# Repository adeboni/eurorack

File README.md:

This repository stores various eurorack module designs I've made.

* BT Module: Allows you to pair your phone or computer and outputs stereo audio
* Dodecamodulator: 12 individually configurable LFOs through an onboard UI or through Bluetooth
* Geiger Clock Module: Uses a Geiger–Müller tube to generate pulses
* Google Assistant Module: A Google Home Mini in a eurorack form-factor
* Neopixel Controller Module: Can control neopixel rainbow cycle speed, brightness, and VU-meter-style amplitude with CV
* CS:GO Game State Integration Server: Receives events from CS:GO and enables gate outputs based on game states
* Safety Valve: Update of the GSMN Safety Safety Valve module with a trimmer to remove op-amp offset and added a socket for the tube
* ECG: Outputs a waveform from ECG electrodes plus a gate output with threshold adjustment

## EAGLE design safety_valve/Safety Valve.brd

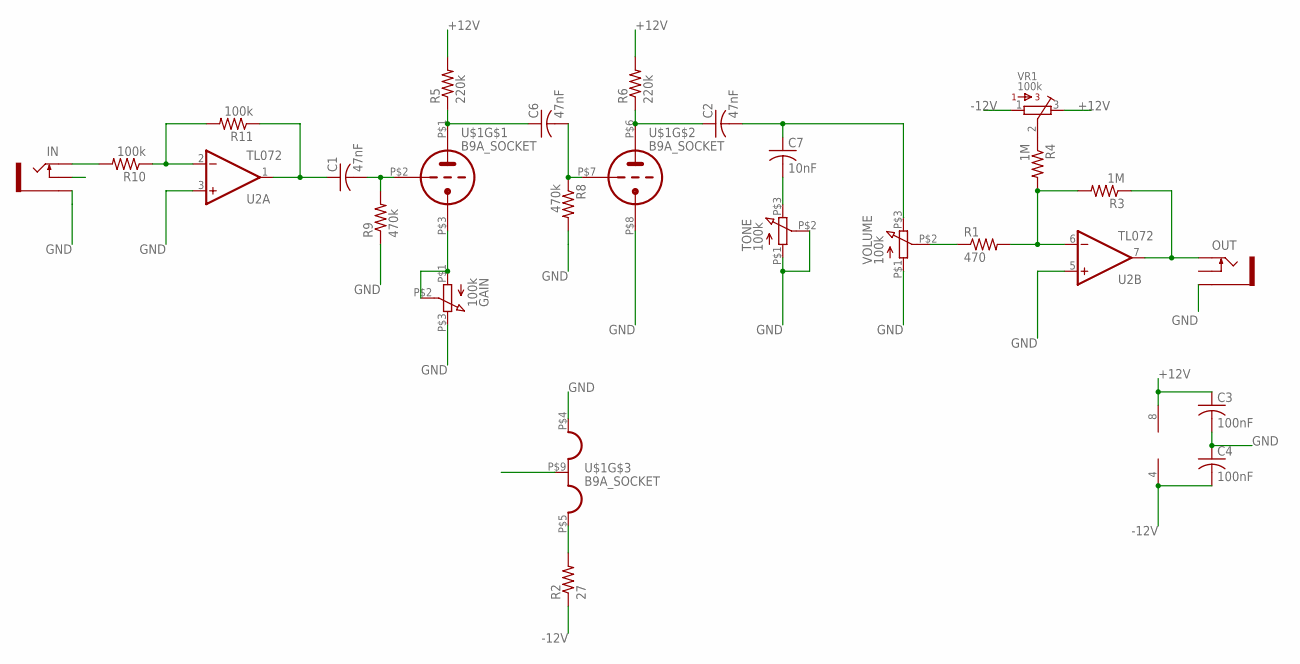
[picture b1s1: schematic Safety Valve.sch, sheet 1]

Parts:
C1, C2, C6: 47nF; C025-024X044
C3, C4: 100nF; C025-024X044
C7: 10nF; C050-024X044
GAIN: 100k; POTENTIOMETER_9MM
IN: SOCKET_MONO_3.5MMPJ301M-12; PJ301M-12
OUT: SOCKET_MONO_3.5MMPJ301M-12; PJ301M-12
R1: 470; 0207/10
R2: 27; 0207/15
R3, R4: 1M; 0207/10
R5, R6: 220k; 0207/10
R8, R9: 470k; 0207/10
R10, R11: 100k; 0207/10
TONE: 100k; POTENTIOMETER_9MM
U2: TL072; DIL08-SML
U$1: B9A_SOCKET
VOLUME: 100k; POTENTIOMETER_9MM
VR1: 100k; BOURNS_3362P_TRIMMER

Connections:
+12V: C3.1, R5.2, R6.2, U2.8 (V+), VR1.3; also elsewhere on the board
-12V: C4.2, R2.1, U2.4 (V-), VR1.1; also elsewhere on the board
GND: C3.2, C4.1, GAIN.P$3 (3), IN.GND (SLEEVE), OUT.GND (SLEEVE), R8.2, R9.1, TONE.P$1 (1), TONE.P$2 (2), U2.3 (+IN), U2.5 (+IN), U$1.P$4 (H1), U$1.P$8 (TK), VOLUME.P$1 (1); also elsewhere on the board
unnamed: GAIN.P$1 (1), GAIN.P$2 (2), U$1.P$3 (TK)
unnamed: R1.2, R3.2, R4.2, U2.6 (-IN)
unnamed: C2.2, C7.1, VOLUME.P$3 (3)
unnamed: OUT.TIP, R3.1, U2.7 (OUT)
unnamed: C2.1, R6.1, U$1.P$6 (TA)
unnamed: C6.1, R5.1, U$1.P$1 (TA)
unnamed: C1.2, R9.2, U$1.P$2 (TG)
unnamed: R4.1, VR1.2
unnamed: C1.1, R11.1, U2.1 (OUT)
unnamed: R2.2, U$1.P$5 (H3)
unnamed: C6.2, R8.1, U$1.P$7 (TG)
unnamed: IN.TIP, R10.2
unnamed: C7.2, TONE.P$3 (3)
unnamed: R10.1, R11.2, U2.2 (-IN)
unnamed: R1.1, VOLUME.P$2 (2)

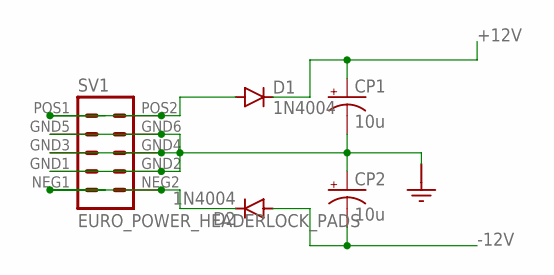
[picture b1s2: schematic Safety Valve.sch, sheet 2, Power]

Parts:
CP1, CP2: 10u; SANYO-OSCON_D
D1, D2: 1N4004; DO41-10
SV1: EURO_POWER_HEADERLOCK_PADS; EURO_PWR_HEADER_LOCK

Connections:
+12V: CP1.+, D1.C; also elsewhere on the board
-12V: CP2.-, D2.A; also elsewhere on the board
GND: CP1.-, CP2.+, SV1.GND1 (4), SV1.GND2 (3), SV1.GND3 (6), SV1.GND4 (5), SV1.GND5 (8), SV1.GND6 (7); also elsewhere on the board
unnamed: D1.A, SV1.POS1 (10), SV1.POS2 (9)
unnamed: D2.C, SV1.NEG1 (2), SV1.NEG2 (1)

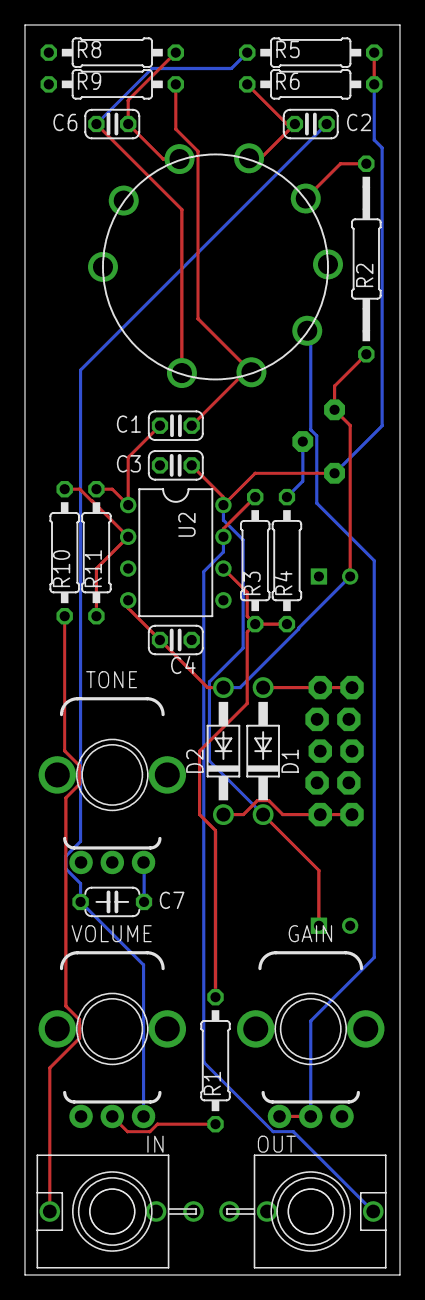
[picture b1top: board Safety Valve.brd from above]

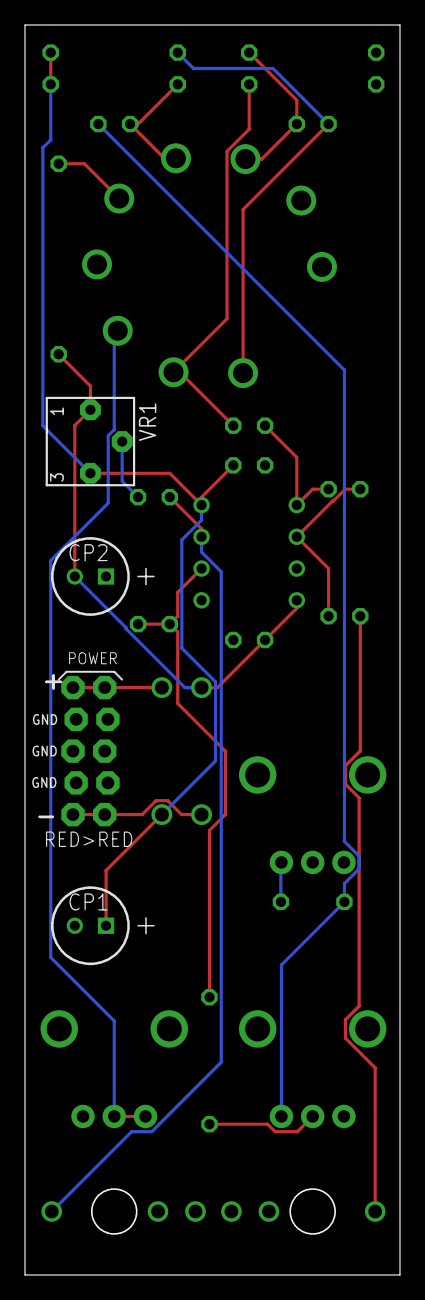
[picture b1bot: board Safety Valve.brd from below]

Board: 2 copper layers, 29.9 x 99.9 mm, 29 parts (4 on the bottom side), 20 nets.

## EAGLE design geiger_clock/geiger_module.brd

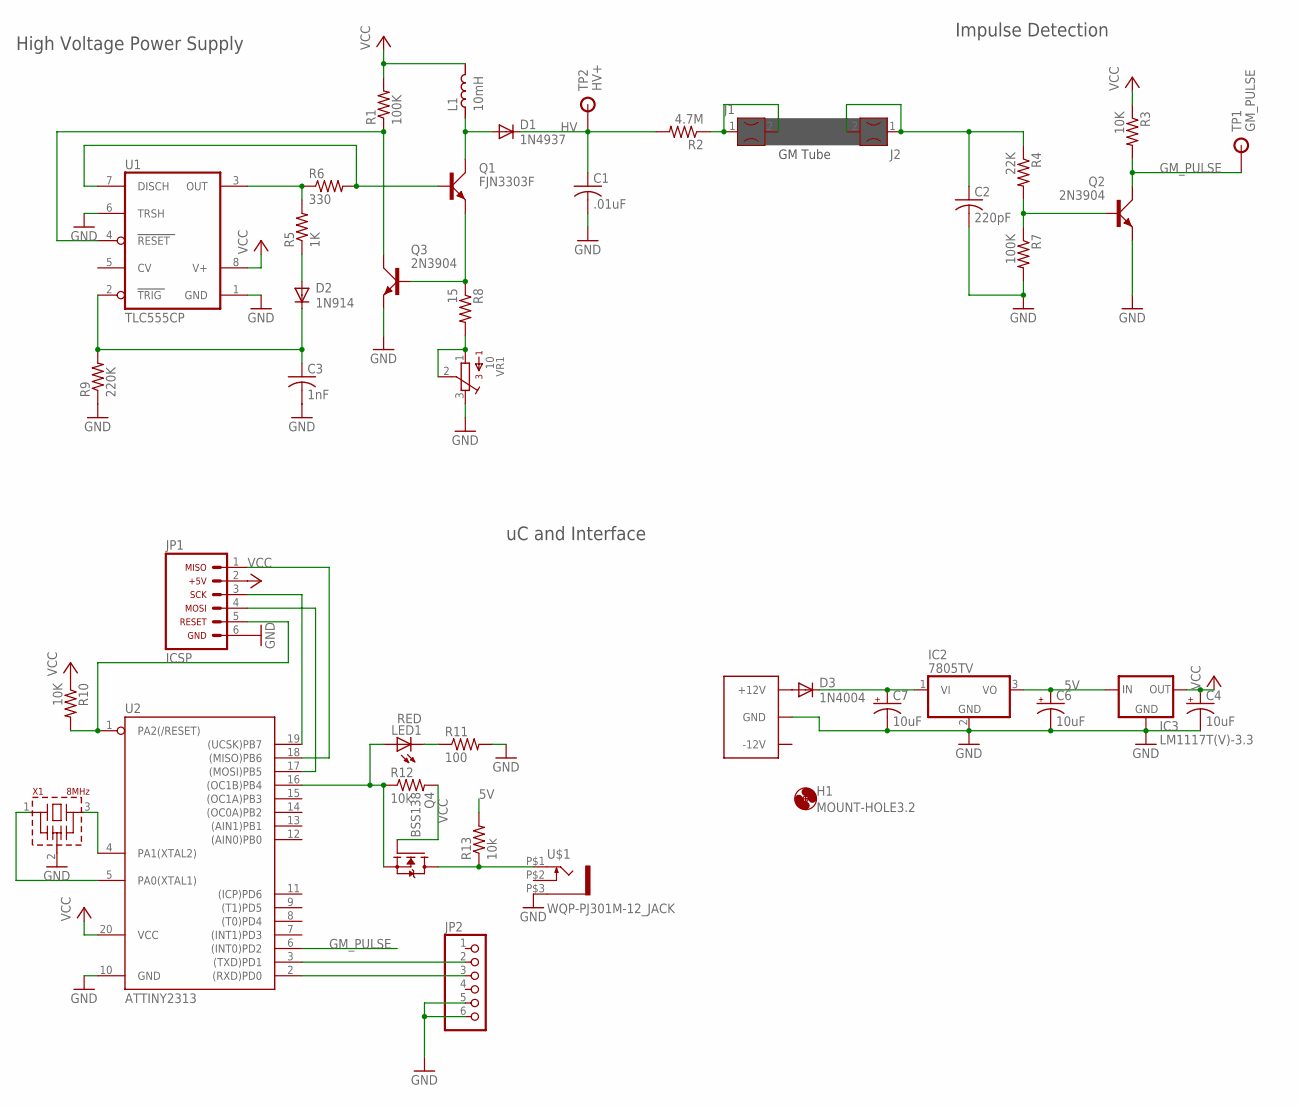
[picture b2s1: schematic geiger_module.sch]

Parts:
C1: .01uF; C102-043X133
C2: 220pF; C050-030X075
C3: 1nF; C050-025X075
C4, C6, C7: 10uF; CPOL-RADIAL-2.5MM-5MM
C8: EURO_POWER_LOCKSKINNY; EURO_POWER_HEADER
D1: 1N4937; DO41-10
D2: 1N914; DO35-7
D3: 1N4004; DO41-10
H1: MOUNT-HOLE3.2; 3,2
IC2: 7805TV; TO220V
IC3: LM1117T(V)-3.3; TO220V
J1, J2: FUSECLIPPCMOUNT; FUSECLIP_PCMOUNT
JP1: ARDUINO_CONN-ICSP; CONN-2X03
JP2: PINHD-1X6; 1X06
L1: 10mH; ELC09D
LED1: RED; LED5MM
Q1: FJN3303F; TO92C
Q2, Q3: 2N3904; TO92D
Q4: BSS138; SOT23
R1, R7: 100K; 0207/10
R2: 4.7M; 0207/10
R3, R10: 10K; 0207/10
R4: 22K; 0207/10
R5: 1K; 0207/10
R6: 330; 0207/10
R8: 15; 0207/10
R9: 220K; 0207/10
R11: 100; 0207/10
R12, R13: 10k; 0207/10
TP1: GM_PULSE; TP_PTH
TP2: HV+; TP_PTH
U1: TLC555CP; DIL08
U2: ATTINY2313; DIL20
U$1: WQP-PJ301M-12_JACK
VR1: 10; 3386P
X1: 8MHz; CSTLA_T

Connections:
5V: C6.1 (+), IC2.3 (VO), IC3.3 (IN), R13.2
12V: C7.1 (+), D3.C, IC2.1 (VI)
GM_PULSE: Q2.C, R3.2, TP1.P$1, U2.6 ((INT0)PD2)
GND: C1.2, C2.2, C3.2, C4.2 (-), C6.2 (-), C7.2 (-), C8.3 (GND), C8.4 (GND), C8.5 (GND), C8.6 (GND), C8.7 (GND), C8.8 (GND), IC2.2 (GND), IC3.1 (GND), JP1.6, JP2.5, JP2.6, Q2.E, Q3.E, R7.2, R9.1, R11.2, U1.1 (GND), U1.6 (TRSH), U2.10 (GND), U$1.P$3 (1), VR1.3, X1.2 (VSS)
HV: C1.1, D1.C, R2.2, TP2.P$1
unnamed: D2.A, R5.1
unnamed: JP1.5, R10.2, U2.1 (PA2(/RESET))
unnamed: Q3.C, R1.1, U1.4 (RESET)
unnamed: C8.9 (+12V), C8.10 (+12V), D3.A
unnamed: JP1.3, U2.19 ((UCSK)PB7)
unnamed: JP2.2, U2.3 ((TXD)PD1)
unnamed: JP2.3, U2.2 ((RXD)PD0)
unnamed: Q1.B, R6.2, U1.7 (DISCH)
unnamed: C3.1, D2.C, R9.2, U1.2 (TRIG)
unnamed: R5.2, R6.1, U1.3 (OUT)
unnamed: Q1.E, Q3.B, R8.1
unnamed: D1.A, L1.1, Q1.C
unnamed: JP1.1, U2.18 ((MISO)PB6)
unnamed: Q2.B, R4.2, R7.1
unnamed: J1.1, J1.2, R2.1
unnamed: JP1.4, U2.17 ((MOSI)PB5)
unnamed: U2.4 (PA1(XTAL2)), X1.3
unnamed: U2.5 (PA0(XTAL1)), X1.1
unnamed: LED1.K (C), R11.1
unnamed: R8.2, VR1.1, VR1.2
unnamed: C2.1, J2.1, J2.2, R4.1
PIN16: LED1.A, Q4.2 (S), R12.1, U2.16 ((OC1B)PB4)
PIN165V: Q4.3 (D), R13.1, U$1.P$1 (2)
VCC: C4.1 (+), IC3.2 (OUT), JP1.2, L1.2, Q4.1 (G), R1.2, R3.1, R10.1, R12.2, U1.8 (V+), U2.20 (VCC)

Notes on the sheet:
GM Tube
High Voltage Power Supply
Impulse Detection
uC and Interface

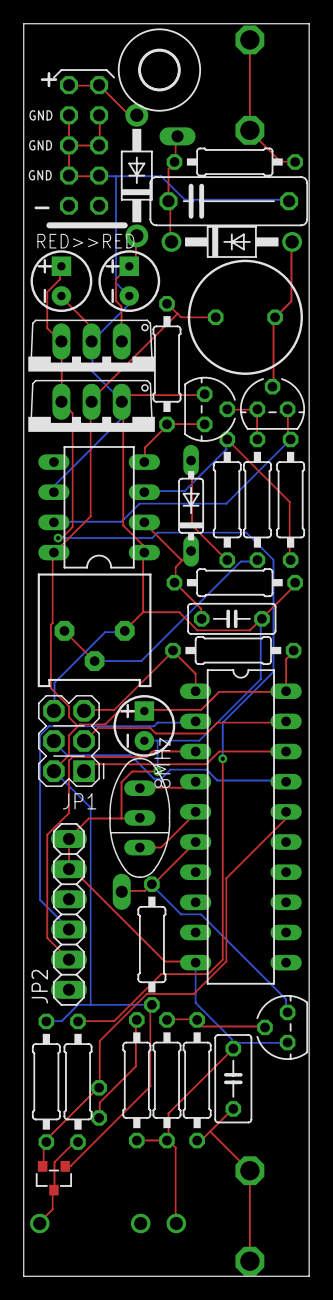
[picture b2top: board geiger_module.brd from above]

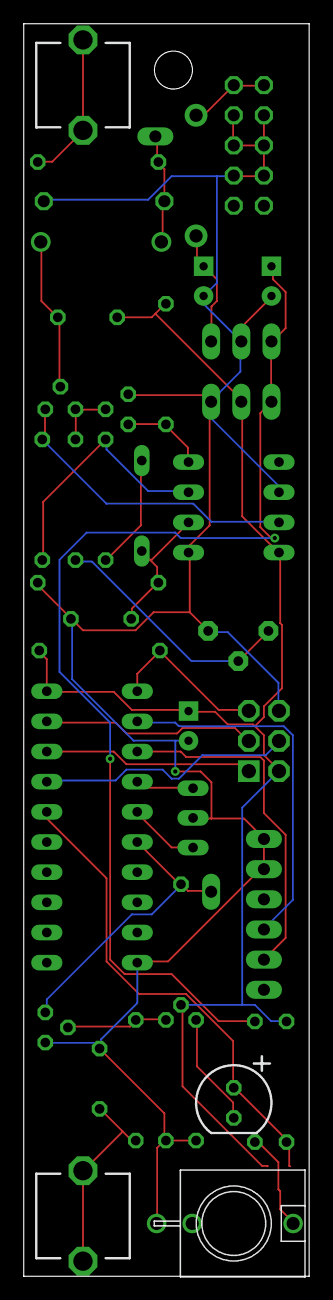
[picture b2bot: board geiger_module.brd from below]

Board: 2 copper layers, 24.0 x 105.5 mm, 43 parts (4 on the bottom side), 29 nets.

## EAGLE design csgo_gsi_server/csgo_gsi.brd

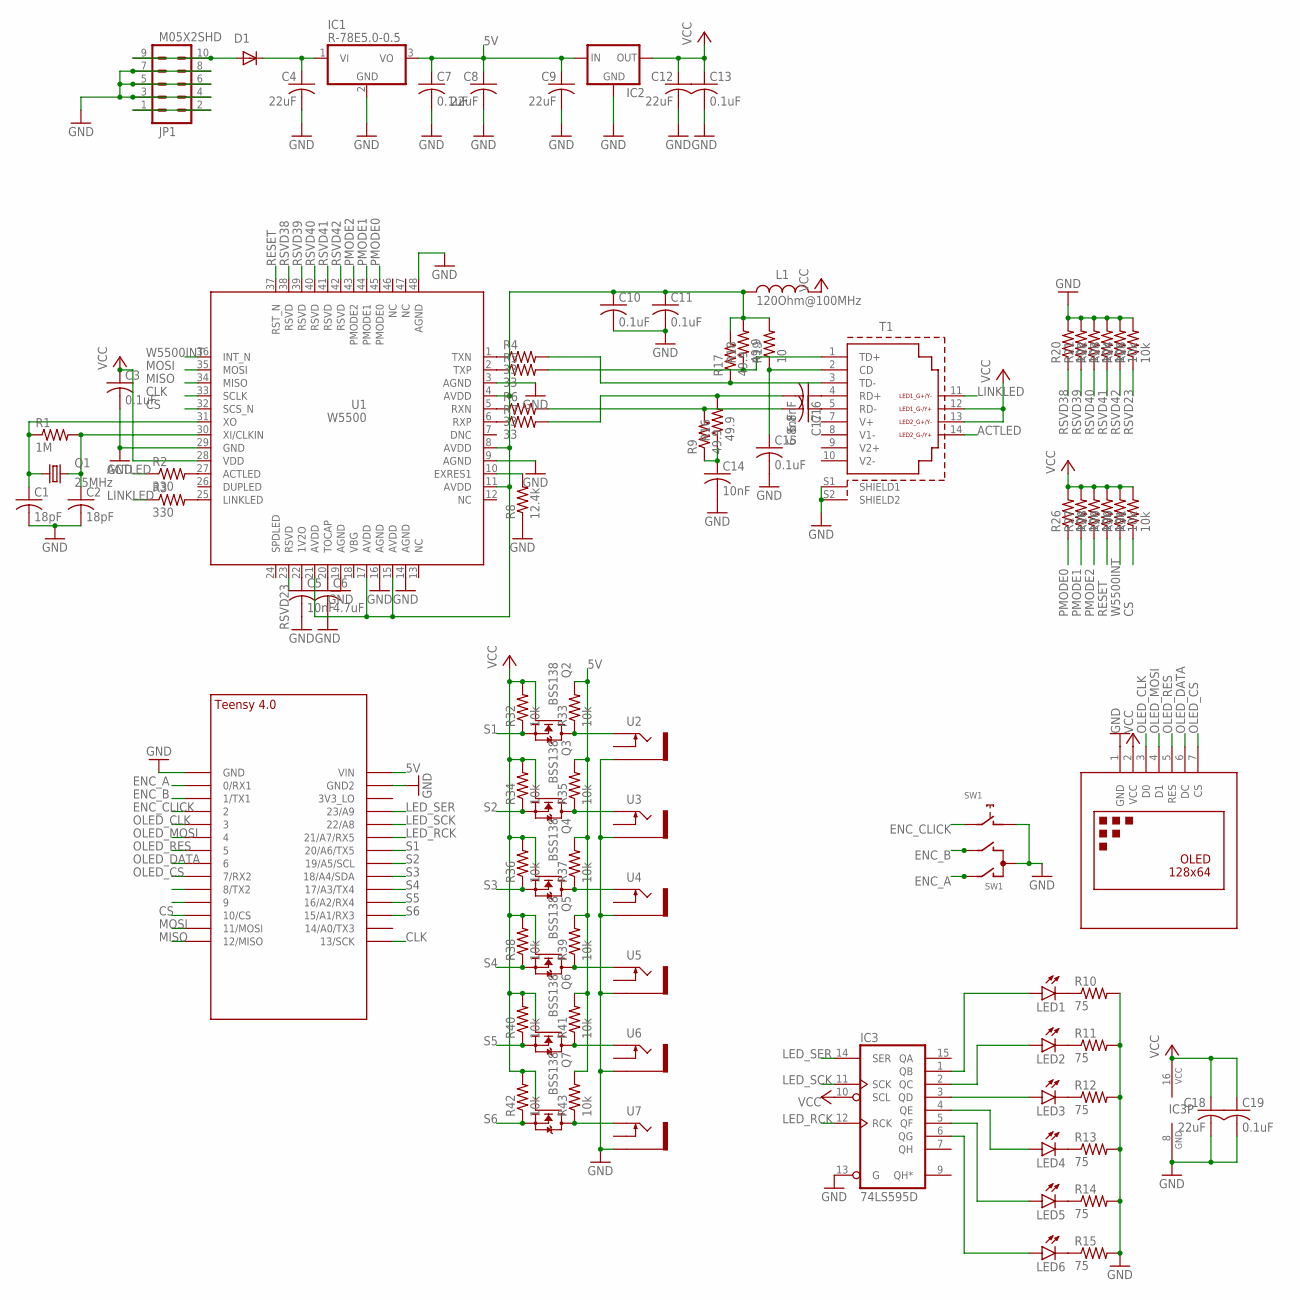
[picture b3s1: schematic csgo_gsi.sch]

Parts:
C1, C2: 18pF; C0603
C3, C7, C10, C11, C13, C15, C19: 0.1uF; C0603
C4, C8, C9, C12, C18: 22uF; C1206
C5, C14: 10nF; C0603
C6: 4.7uF; C0603
C16, C17: 6.8nF; C0603
D1: 1N5819HW; SOD123
IC1: R-78E5.0-0.5; WE78
IC2: LM1117; SOT223
IC3: 74LS595D; SO16
JP1: M05X2SHD; 2X5-SHROUDED
L1: 120Ohm@100MHz; WE-CBF_0603(W=2.2)
LED1, LED2, LED3, LED4, LED5, LED6: LED3MM
OLED1: DISPLAY-OLED-128X64
Q1: 25MHz; 3.2X2.5_KX-7
Q2, Q3, Q4, Q5, Q6, Q7: BSS138; SOT23
R1: 1M; R0603
R2, R3: 330; R0603
R4, R5, R6, R7: 33; R0603
R8: 12.4k; R0603
R9, R16, R17, R18: 49.9; R0603
R10, R11, R12, R13, R14, R15: 75; R0603
R19: 10; R0603
R20, R21, R22, R23, R24, R25, R26, R27, R28, R29, R30, R31, R32, R33, R34, R35, R36, R37, R38, R39, R40, R41, R42, R43: 10k; R0603
SW1: Encoder; ALPS_EC12E_SW
T1: WE-RJ45_74984104401; 74984104401
U1: W5500
U2, U3, U4, U5, U6, U7: THONKICONNNEW; WQP-PJ301M-12_JACK
U$1: TEENSY_4.0-BASIC

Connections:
5V: C7.1, C8.1, C9.1, IC1.3 (VO), IC2.3 (IN), R33.2, R35.2, R37.2, R39.2, R41.2, R43.2, U$1.VIN
12V: C4.1, D1.C, IC1.1 (VI)
ACTLED: R2.1, T1.14 (LED2_Y+/G-)
CLK: U1.33 (SCLK), U$1.13/SCK
CS: R31.1, U1.32 (SCS_N), U$1.10/CS
ENC_A: SW1.A, U$1.0/RX (0/RX1)
ENC_B: SW1.B, U$1.1/TX (1/TX1)
ENC_CLICK: SW1.E (2), U$1.2
GND: C1.2, C2.2, C3.2, C4.2, C5.2, C6.2, C7.2, C8.2, C9.2, C10.2, C11.2, C12.2, C13.2, C14.2, C15.2, C18.2, C19.2, IC1.2 (GND), IC2.1 (GND), IC3.8 (GND), IC3.13 (G), JP1.3, JP1.4, JP1.5, JP1.6, JP1.7, JP1.8, OLED1.1 (GND), R8.1, R10.2, R11.2, R12.2, R13.2, R14.2, R15.2, R20.2, R21.2, R22.2, R23.2, R24.2, R25.2, SW1.C, SW1.D (1), T1.S1 (SHIELD1), T1.S2 (SHIELD2), U1.3 (AGND), U1.9 (AGND), U1.14 (AGND), U1.16 (AGND), U1.19 (AGND), U1.29 (GND), U1.48 (AGND), U2.P$3_SLEEVE (SLEEVE), U3.P$3_SLEEVE (SLEEVE), U4.P$3_SLEEVE (SLEEVE), U5.P$3_SLEEVE (SLEEVE), U6.P$3_SLEEVE (SLEEVE), U7.P$3_SLEEVE (SLEEVE), U$1.GND
LED1: IC3.1 (QB), LED1.A
LED2: IC3.2 (QC), LED2.A
LED3: IC3.3 (QD), LED3.A
LED4: IC3.4 (QE), LED4.A
LED5: IC3.5 (QF), LED5.A
LED6: IC3.6 (QG), LED6.A
LED_RCK: IC3.12 (RCK), U$1.21/A7 (21/A7/RX5)
LED_SCK: IC3.11 (SCK), U$1.22/A8
LED_SER: IC3.14 (SER), U$1.23/A9
LINKLED: R3.1, T1.11 (LED1_Y-/G+)
MISO: U1.34 (MISO), U$1.12/MISO
MOSI: U1.35 (MOSI), U$1.11/MOSI
unnamed: C5.1, U1.22 (1V2O)
unnamed: C6.1, U1.20 (TOCAP)
unnamed: R5.2, R18.1, T1.1 (TD+)
unnamed: R4.2, R17.1, T1.3 (TD-)
unnamed: R3.2, U1.25 (LINKLED)
unnamed: R2.2, U1.27 (ACTLED)
unnamed: R8.2, U1.10 (EXRES1)
unnamed: R4.1, U1.1 (TXN)
unnamed: R5.1, U1.2 (TXP)
unnamed: R6.1, U1.5 (RXN)
unnamed: R7.1, U1.6 (RXP)
unnamed: C16.1, T1.4 (RD+)
unnamed: C17.1, T1.5 (RD-)
unnamed: C16.2, R7.2, R16.2
unnamed: C17.2, R6.2, R9.2
unnamed: C14.1, R9.1, R16.1
unnamed: C1.1, Q1.1, R1.1, U1.31 (XO)
unnamed: C15.1, R19.1, T1.2 (CD)
unnamed: C10.1, C11.1, L1.1, R17.2, R18.2, R19.2, U1.4 (AVDD), U1.8 (AVDD), U1.11 (AVDD), U1.15 (AVDD), U1.17 (AVDD), U1.21 (AVDD)
unnamed: C2.1, Q1.3 (2), R1.2, U1.30 (XI/CLKIN)
unnamed: LED1.K (C), R10.1
unnamed: Q2.3 (D), R33.1, U2.P$1_TIP (TIP)
unnamed: LED2.K (C), R11.1
unnamed: Q3.3 (D), R35.1, U3.P$1_TIP (TIP)
unnamed: LED3.K (C), R12.1
unnamed: Q4.3 (D), R37.1, U4.P$1_TIP (TIP)
unnamed: LED4.K (C), R13.1
unnamed: Q5.3 (D), R39.1, U5.P$1_TIP (TIP)
unnamed: LED5.K (C), R14.1
unnamed: Q6.3 (D), R41.1, U6.P$1_TIP (TIP)
unnamed: LED6.K (C), R15.1
unnamed: Q7.3 (D), R43.1, U7.P$1_TIP (TIP)
unnamed: D1.A, JP1.9, JP1.10
unnamed: JP1.1, JP1.2
OLED_CLK: OLED1.3 (D0), U$1.3/CANTX (3)
OLED_CS: OLED1.7 (CS), U$1.7 (7/RX2)
OLED_DATA: OLED1.6 (DC), U$1.6
OLED_MOSI: OLED1.4 (D1), U$1.4/CANRX (4)
OLED_RES: OLED1.5 (RES), U$1.5
PMODE0: R26.1, U1.45 (PMODE0)
PMODE1: R27.1, U1.44 (PMODE1)
PMODE2: R28.1, U1.43 (PMODE2)
RESET: R29.1, U1.37 (RST_N)
RSVD23: R25.1, U1.23 (RSVD)
RSVD38: R20.1, U1.38 (RSVD)
RSVD39: R21.1, U1.39 (RSVD)
RSVD40: R22.1, U1.40 (RSVD)
RSVD41: R23.1, U1.41 (RSVD)
RSVD42: R24.1, U1.42 (RSVD)
S1: Q2.2 (S), R32.1, U$1.20/A6 (20/A6/TX5)
S2: Q3.2 (S), R34.1, U$1.19/A5/SCL
S3: Q4.2 (S), R36.1, U$1.18/A4/SDA
S4: Q5.2 (S), R38.1, U$1.17/A3 (17/A3/TX4)
S5: Q6.2 (S), R40.1, U$1.16/A2 (16/A2/RX4)
S6: Q7.2 (S), R42.1, U$1.15/A1 (15/A1/RX3)
VCC: C3.1, C12.1, C13.1, C18.1, C19.1, IC2.2 (OUT), IC3.10 (SCL), IC3.16 (VCC), L1.2, OLED1.2 (VCC), Q2.1 (G), Q3.1 (G), Q4.1 (G), Q5.1 (G), Q6.1 (G), Q7.1 (G), R26.2, R27.2, R28.2, R29.2, R30.2, R31.2, R32.2, R34.2, R36.2, R38.2, R40.2, R42.2, T1.12 (LED1_Y+/G-), T1.13 (LED2_Y-/G+), U1.28 (VDD)
W5500INT: R30.1, U1.36 (INT_N)

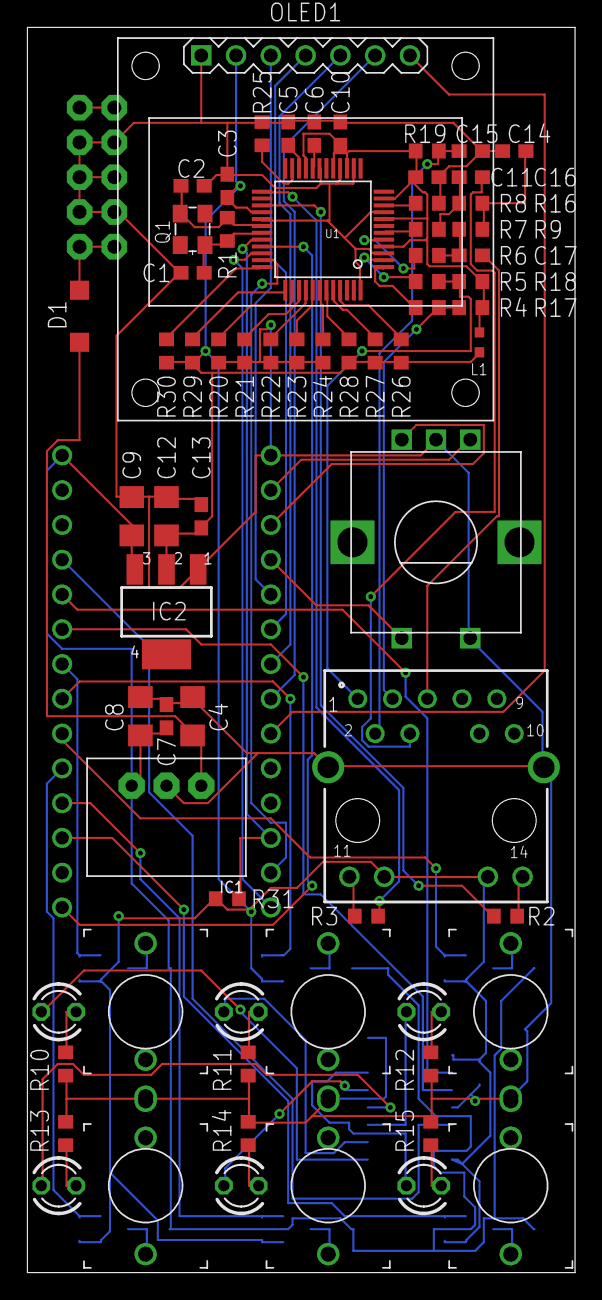
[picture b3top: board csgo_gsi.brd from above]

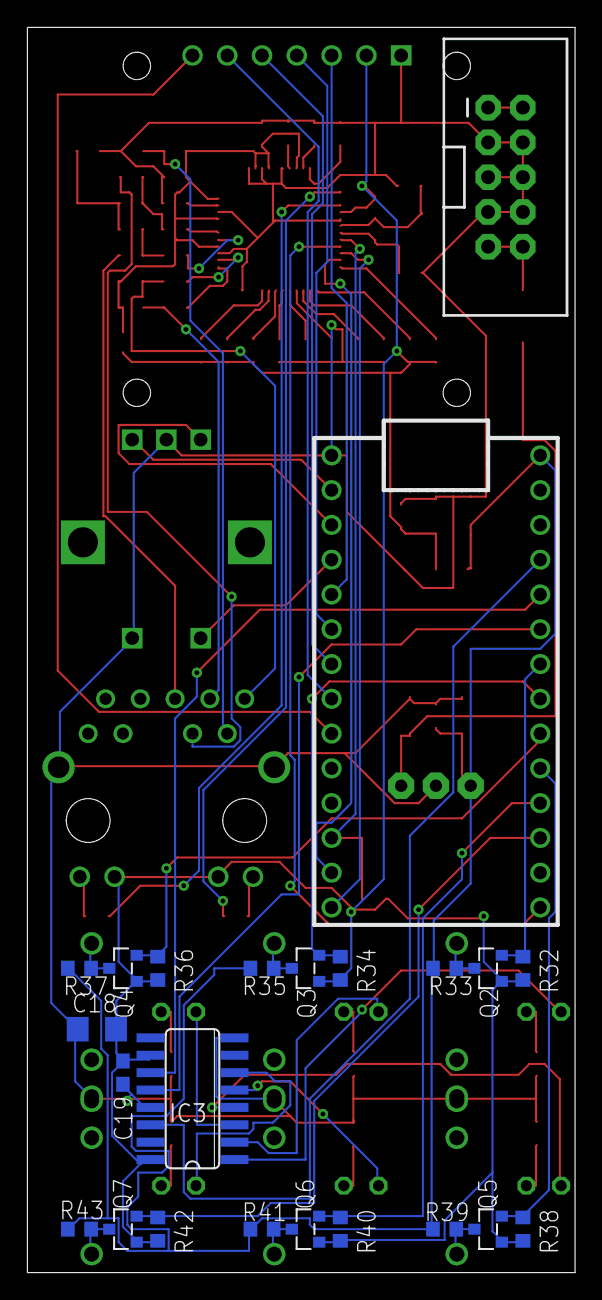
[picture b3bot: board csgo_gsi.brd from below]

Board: 2 copper layers, 40.0 x 91.0 mm, 92 parts (23 on the bottom side), 78 nets.

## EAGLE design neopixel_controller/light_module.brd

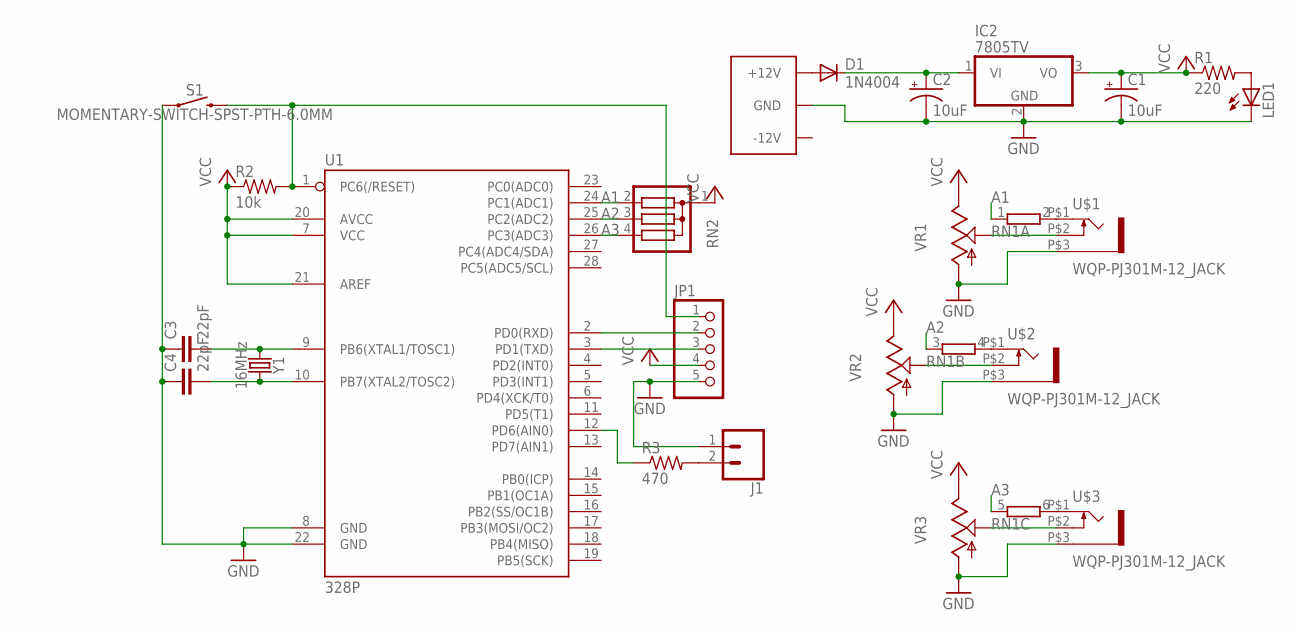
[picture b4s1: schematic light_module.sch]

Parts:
C1, C2: 10uF; CPOL-RADIAL-2.5MM-5MM
C3, C4: 22pF; CAP-PTH-2.54
C5: EURO_POWER_LOCKSKINNY; EURO_POWER_HEADER
D1: 1N4004; DO41-10
IC2: 7805TV; TO220V
J1: CONN_02SPRING-2.54-RA; SPRINGTERMINAL-2.54MM-2
JP1: PINHD-1X5; 1X05
LED1: LED5MM
R1: 220; 0207/2V
R2: 10k; 0207/2V
R3: 470; 0207/2V
RN1: E3R; SIL6
RN2: G03R; SIL4
S1: MOMENTARY-SWITCH-SPST-PTH-6.0MM; TACTILE_SWITCH_PTH_6.0MM
U1: 328P; DIP28
U$1, U$2, U$3: WQP-PJ301M-12_JACK
VR1, VR2, VR3: 9MM_SNAP-IN_POT_; 9MM_SNAP-IN_POT
Y1: 16MHz; HC49US

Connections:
A1: RN1.1, RN2.2, U1.24 (PC1(ADC1))
A2: RN1.3 (1), RN2.3, U1.25 (PC2(ADC2))
A3: RN1.5 (1), RN2.4, U1.26 (PC3(ADC3))
GND: C1.2 (-), C2.2 (-), C3.1, C4.1, C5.3 (GND), C5.4 (GND), C5.5 (GND), C5.6 (GND), C5.7 (GND), C5.8 (GND), IC2.2 (GND), J1.1, JP1.5, LED1.K (C), S1.1, U1.8 (GND), U1.22 (GND), U$1.P$3 (1), U$2.P$3 (1), U$3.P$3 (1), VR1.1 (A), VR2.1 (A), VR3.1 (A)
unnamed: C5.9 (+12V), C5.10 (+12V), D1.A
unnamed: C2.1 (+), D1.C, IC2.1 (VI)
unnamed: LED1.A, R1.2
unnamed: JP1.1, R2.2, S1.3 (2), U1.1 (PC6(/RESET))
unnamed: C3.2, U1.9 (PB6(XTAL1/TOSC1)), Y1.1
unnamed: C4.2, U1.10 (PB7(XTAL2/TOSC2)), Y1.2
unnamed: JP1.2, U1.2 (PD0(RXD))
unnamed: JP1.3, U1.3 (PD1(TXD))
unnamed: U$1.P$2 (3), VR1.2 (S)
unnamed: U$2.P$2 (3), VR2.2 (S)
unnamed: U$3.P$2 (3), VR3.2 (S)
unnamed: J1.2, R3.2
unnamed: R3.1, U1.12 (PD6(AIN0))
unnamed: RN1.2, U$1.P$1 (2)
unnamed: RN1.4 (2), U$2.P$1 (2)
unnamed: RN1.6 (2), U$3.P$1 (2)
VCC: C1.1 (+), IC2.3 (VO), JP1.4, R1.1, R2.1, RN2.1, U1.7 (VCC), U1.20 (AVCC), U1.21 (AREF), VR1.3 (E), VR2.3 (E), VR3.3 (E)

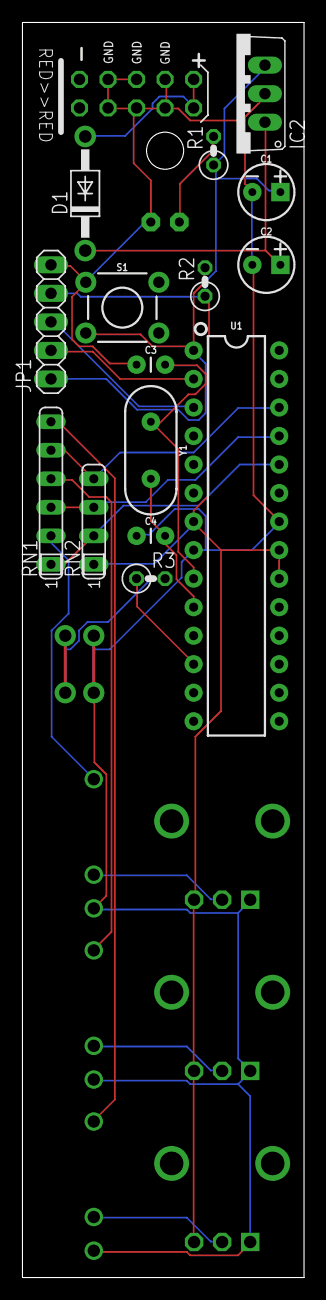
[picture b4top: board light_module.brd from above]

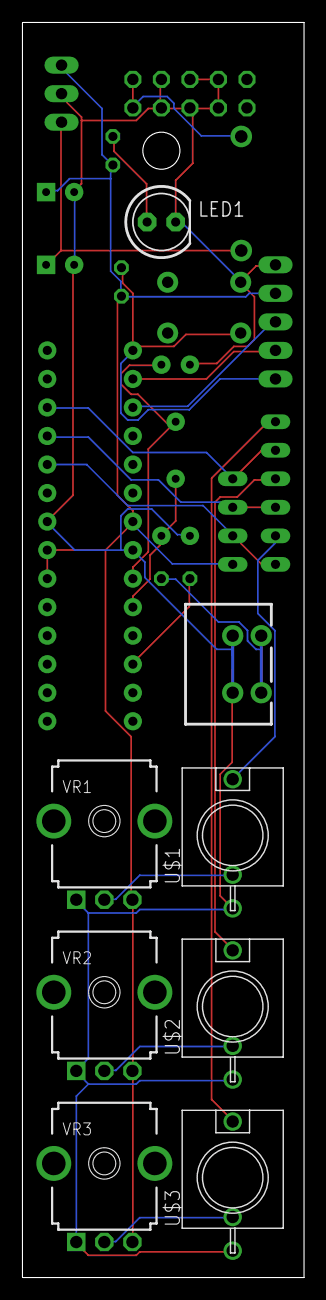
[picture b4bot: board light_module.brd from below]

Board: 2 copper layers, 25.1 x 111.8 mm, 24 parts (8 on the bottom side), 21 nets.

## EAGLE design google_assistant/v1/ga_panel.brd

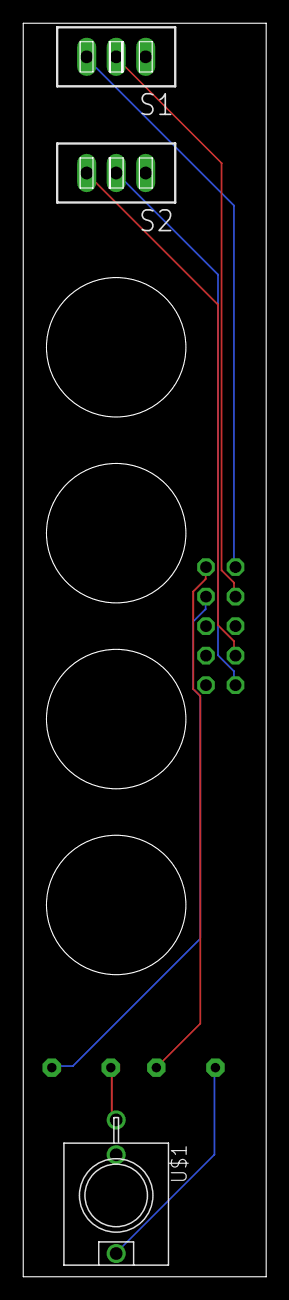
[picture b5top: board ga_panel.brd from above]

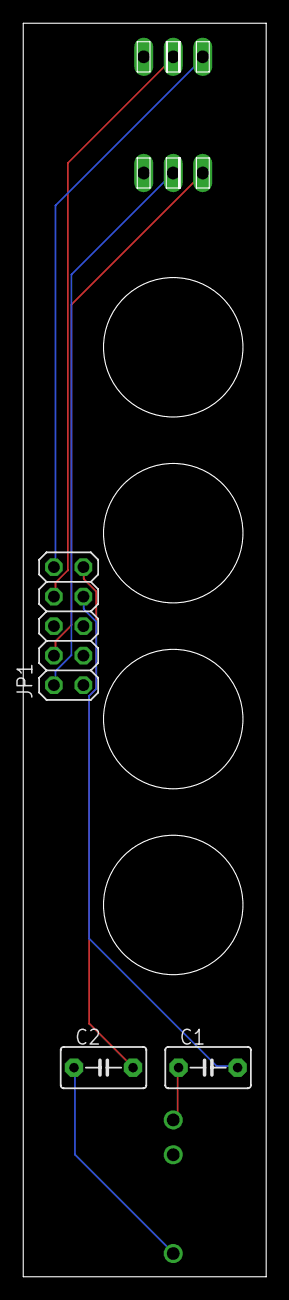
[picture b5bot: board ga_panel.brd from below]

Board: 2 copper layers, 20.9 x 107.9 mm, 6 parts (3 on the bottom side), 8 nets.

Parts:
C1, C2: 10uF; C5B3.5
JP1: 2X05
S1, S2: TL32PO; TL3XPO
U$1: WQP-PJ301M-12_JACK

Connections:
GND: C1.1, U$1.P$3
unnamed: JP1.4, S2.3
unnamed: JP1.2, S2.2
unnamed: C1.2, JP1.7
unnamed: JP1.10, S1.3
unnamed: C2.1, U$1.P$1
unnamed: C2.2, JP1.9
unnamed: JP1.8, S1.2

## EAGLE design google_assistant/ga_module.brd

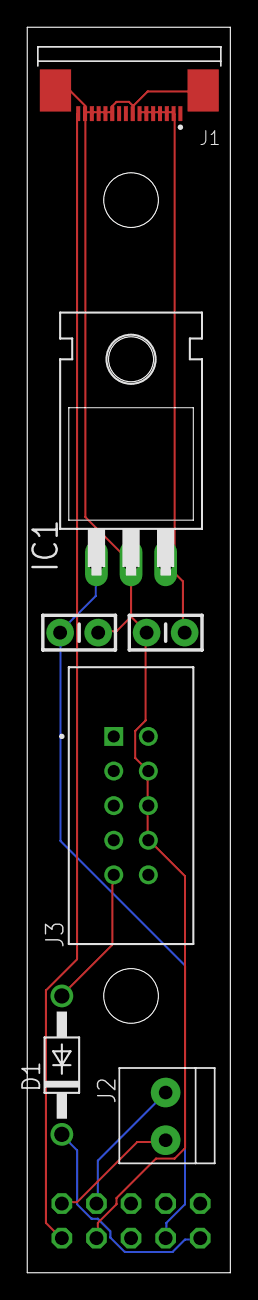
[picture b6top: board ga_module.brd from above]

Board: 2 copper layers, 14.9 x 91.4 mm, 8 parts (1 on the bottom side), 8 nets.

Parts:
C1: 0.33uF; CAP-PTH-SMALL-KIT
C2: 0.1uF; CAP-PTH-SMALL-KIT
D1: 1N4004; DO41-10
IC1: 7805T; TO220H
J1: 1-1734839-6; TE_1-1734839-6
J2: 1X2-3.5MM
J3: 5103308-1; TE_5103308-1
JP1: 2X05/90

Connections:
GND: C1.2, C2.2, IC1.2, J1.8, J1.11, J1.12, J1.13, J1.14, J1.15, J1.S1, J1.S2, J3.4, J3.6, J3.8, JP1.4
unnamed: D1.A, J3.9
unnamed: J2.2, JP1.1
unnamed: J1.16, JP1.2
unnamed: C2.1, IC1.3, J1.2, J1.3, J1.4, J1.5, J1.6, J1.7
unnamed: J2.1, JP1.3
unnamed: D1.C, JP1.10
unnamed: C1.1, IC1.1, JP1.8

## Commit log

2019-07-09 added front panels
2019-07-10 added code
2019-07-12 added fiber optics mounting bracket
2020-05-27 added csgo_gsi
2021-03-11 updated the geiger module
2022-02-18 added ecg and safety valve modules
2022-12-08 Create LICENSE
2022-12-08 Added new modules
2023-07-14 Added mindwave alternate firmware
2023-11-15 Updated filenames
2023-11-15 Added carbon mic and milkdrop projects
2024-02-13 Added noise toaster
2024-04-01 Created rev 2
2024-04-10 Fixed FFC connector footprint
2024-05-16 Added missing base resistor
2024-05-16 Added raspberry pi setup
2024-07-23 Added tx2 version of milkdrop
2024-08-14 Create power_bus
2024-08-16 Added mega_12v_pwr
2024-08-16 Updated gerbers
2024-08-19 Added fan connector
2024-08-19 Switched to PWM fan controller
2024-08-20 Added more ground terminals
2024-08-20 Fixed potentiometer polarities
2024-09-18 Updated resistor values
2024-09-24 Moved spade connectors
2024-09-26 Added spring expander
2024-09-27 Added laser controller
2024-10-01 Replaced 3.3V regulator
2024-10-02 Added wand receiver
2024-10-02 Added production files
2024-10-07 Added electrolytic caps
2024-11-26 Added mult
2024-11-27 Updated power bus
2024-12-03 Added keystep expander
2024-12-21 Added transformer
2025-02-07 Updated ga module production files
2025-02-28 Simplified schematic
2025-11-12 Added theremin project
2026-01-08 Updated trace widths and capacitor values

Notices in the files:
parts and their libraries:
o160525v244 Eagle_WE-CBF: Copyright: Würth Elektronik
diy-modules: Released under the Creative Commons Attribution 4.0 International License: http://creativecommons.org/licenses/by/4.0
crystal-geyer_V1_0: Copyright: Geyer-Electronic
